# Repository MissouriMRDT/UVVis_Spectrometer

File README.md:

# UV-Vis-Spectrometer
Project description:
https://mailmissouri.sharepoint.com/:w:/r/sites/SDELC-MarsRoverDesignTeam-Ogrp/Shared%20Documents/%23ROVESODRIVE/2024%20(CURRENT%20YEAR)/2%20-%20Arch%20Electrical/3%20-%20Project%20Documentation/4%20-%20R%26D%20Projects/UV-Vis%20Spectrometer/Project%20Requirements.docx?d=w72d14293cb114edcbd223a42963af513&csf=1&web=1&e=XHPo1l

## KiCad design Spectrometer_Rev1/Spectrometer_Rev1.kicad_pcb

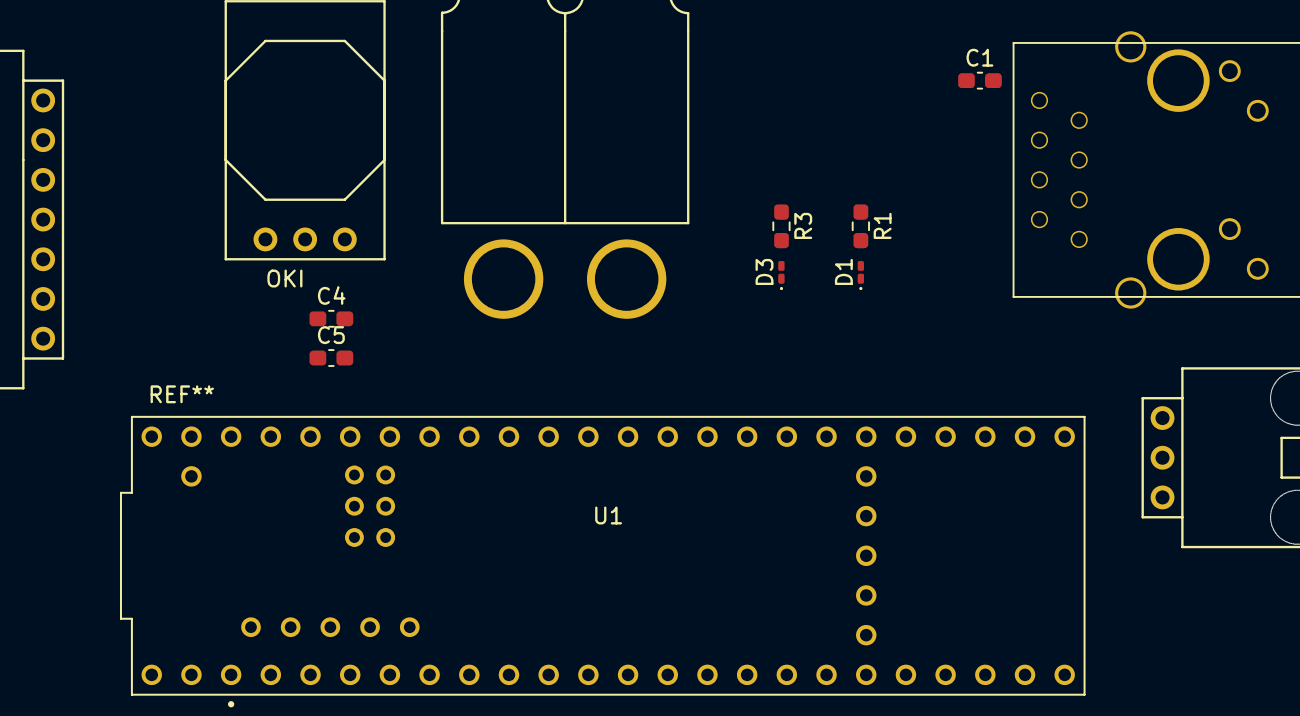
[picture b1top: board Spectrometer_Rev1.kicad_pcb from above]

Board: 2 copper layers, 13 parts (0 on the bottom side), 17 nets, no tracks yet.

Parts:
C1: 0.1uF; C_0603_1608Metric_Pad1.08x0.95mm_HandSolder
C4, C5: 10 UF; C_0603_1608Metric_Pad1.08x0.95mm_HandSolder
Conn1: AndersonPP; Anderson_2_Horizontal_Side_by_Side
Conn3: Molex_SL_07; MOLEX_SL_07_Horizontal
Conn4: Molex_SL_03; MOLEX_SL_03_Horizontal
D1, D3: LED; LED_0201_0603Metric_Pad0.64x0.40mm_HandSolder
J2: RJ45_LED_Shielded; RJ45_Teensy
R1: 300; R_0603_1608Metric_Pad0.98x0.95mm_HandSolder
R3: 1k; R_0603_1608Metric_Pad0.98x0.95mm_HandSolder
U1: Teensy4.1_DEV-16771; Teensy_4_1_Vertical
U3: OKI; OKI_Horizontal

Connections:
+5V: C5.1, Conn3.2, Conn4.2, R1.1, U1.5V, U3.3 (Vo)
+12V: C4.2, Conn1.2 (V+Log), R3.1, U3.1 (Vi)
GND: C1.1, C4.1, C5.2, Conn1.1 (GND), Conn3.1, Conn4.1, D1.1 (K), D3.1 (K), J2.8, J2.9, J2.SH, U1.GND1 (GND), U1.GND2 (GND), U1.GND3 (GND), U1.GND4 (GND), U1.GND5 (GND), U1.USB_GND1 (USB_GND), U1.USB_GND2 (USB_GND), U3.2 (GND)
LED: J2.10, U1.LED
LED_Signal_0: Conn3.3, U1.19 (A5)
LED_Signal_1: Conn3.4, U1.20 (A6)
LED_Signal_2: Conn3.5, U1.21 (A7)
LED_Signal_3: Conn3.6, U1.22 (A8)
LED_Signal_4: Conn3.7, U1.23 (A9)
unnamed: C1.2, J2.2, J2.5
unnamed: D1.2 (A), R1.2
unnamed: D3.2 (A), R3.2
PhotonValue: Conn4.3, U1.38 (A14)
Rx+: J2.4, U1.R+
Rx-: J2.6, U1.R-
Tx+: J2.1, U1.T+
Tx-: J2.3, U1.T-

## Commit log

2023-10-07 Rev_1 design
2023-10-07 Update README.md
    add project description from SharePoint
2023-11-04 switch voltage symbols
2023-11-07 import netlist for layout
